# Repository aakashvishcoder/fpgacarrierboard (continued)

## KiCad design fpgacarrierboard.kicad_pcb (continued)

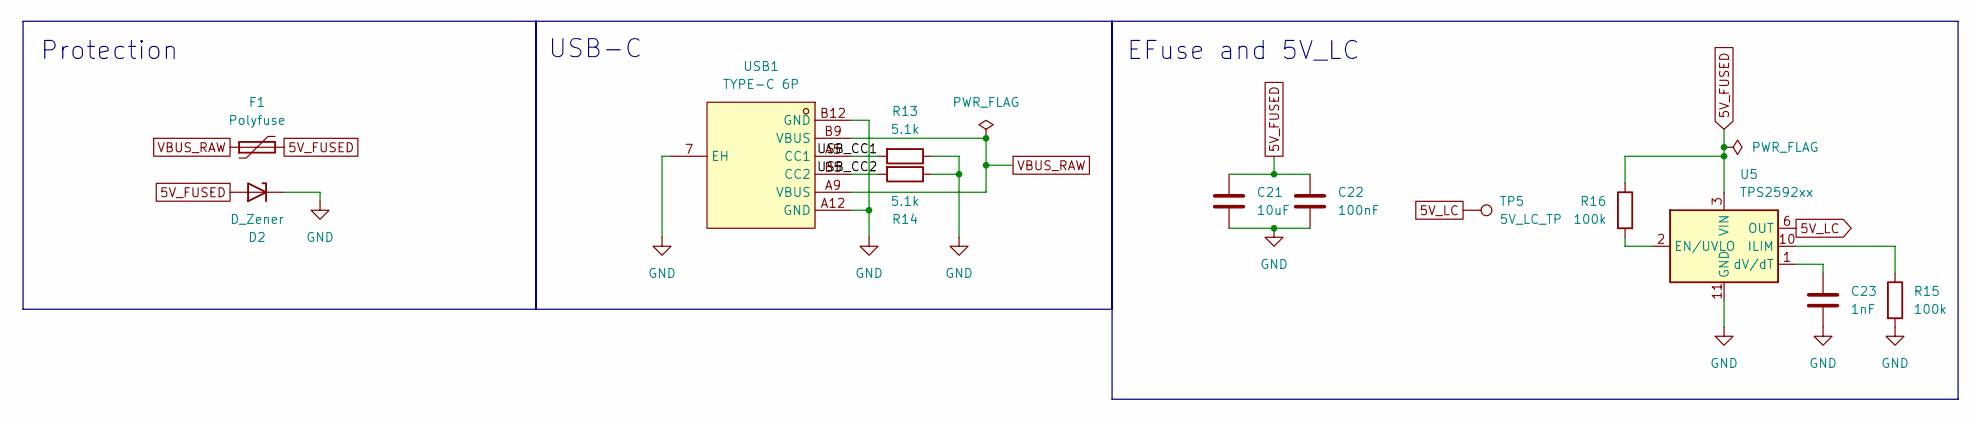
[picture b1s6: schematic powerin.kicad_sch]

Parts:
C21: 10uF; CP_Radial_D5.0mm_P2.00mm; LCSC Part C47344176
C22: 100nF; C_Disc_D3.0mm_W2.0mm_P2.50mm; LCSC Part C5632430
C23: 1nF; C_Disc_D3.0mm_W2.0mm_P2.50mm; LCSC Part C1624895
D2: D_Zener; D_DO-41_SOD81_P10.16mm_Horizontal
F1: Polyfuse; FUSE-TH_L9.5-W3.5-P5.08-D0.8-S1.2
R13, R14: 5.1k; R_Axial_DIN0207_L6.3mm_D2.5mm_P10.16mm_Horizontal
R15, R16: 100k; R_Axial_DIN0207_L6.3mm_D2.5mm_P10.16mm_Horizontal
TP5: 5V_LC_TP; TestPoint_THTPad_D1.5mm_Drill0.7mm
U5: TPS2592xx; VSON-10-1EP_3x3mm_P0.5mm_EP1.65x2.4mm; LCSC Part C527680
USB1: TYPE-C 6P; TYPE-C-SMD_TYPE-C-6P_1; MPN TYPE-C 6P; LCSC Part C456012

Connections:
5V_FUSED: C21.1, C22.1, D2.2 (A), F1.2, R16.1, U5.3 (VIN), U5.4 (VIN), U5.5 (VIN)
5V_LC: TP5.1 (1_1), U5.6 (OUT), U5.7 (OUT), U5.8 (OUT); also elsewhere on the board
/PowerIn/USB_CC1: R13.2, USB1.A5 (CC1)
/PowerIn/USB_CC2: R14.2, USB1.B5 (CC2)
GND: C21.2, C22.2, C23.2, D2.1 (K), R13.1, R14.1, R15.2, U5.11 (GND), USB1.7 (EH), USB1.A12 (GND), USB1.B12 (GND); also elsewhere on the board
unnamed: R16.2, U5.2 (EN/UVLO)
unnamed: R15.1, U5.10 (ILIM)
unnamed: C23.1, U5.1 (dV/dT)
VBUS_RAW: F1.1, USB1.A9 (VBUS), USB1.B9 (VBUS)

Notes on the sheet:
USB-C
Protection
EFuse and 5V_LC

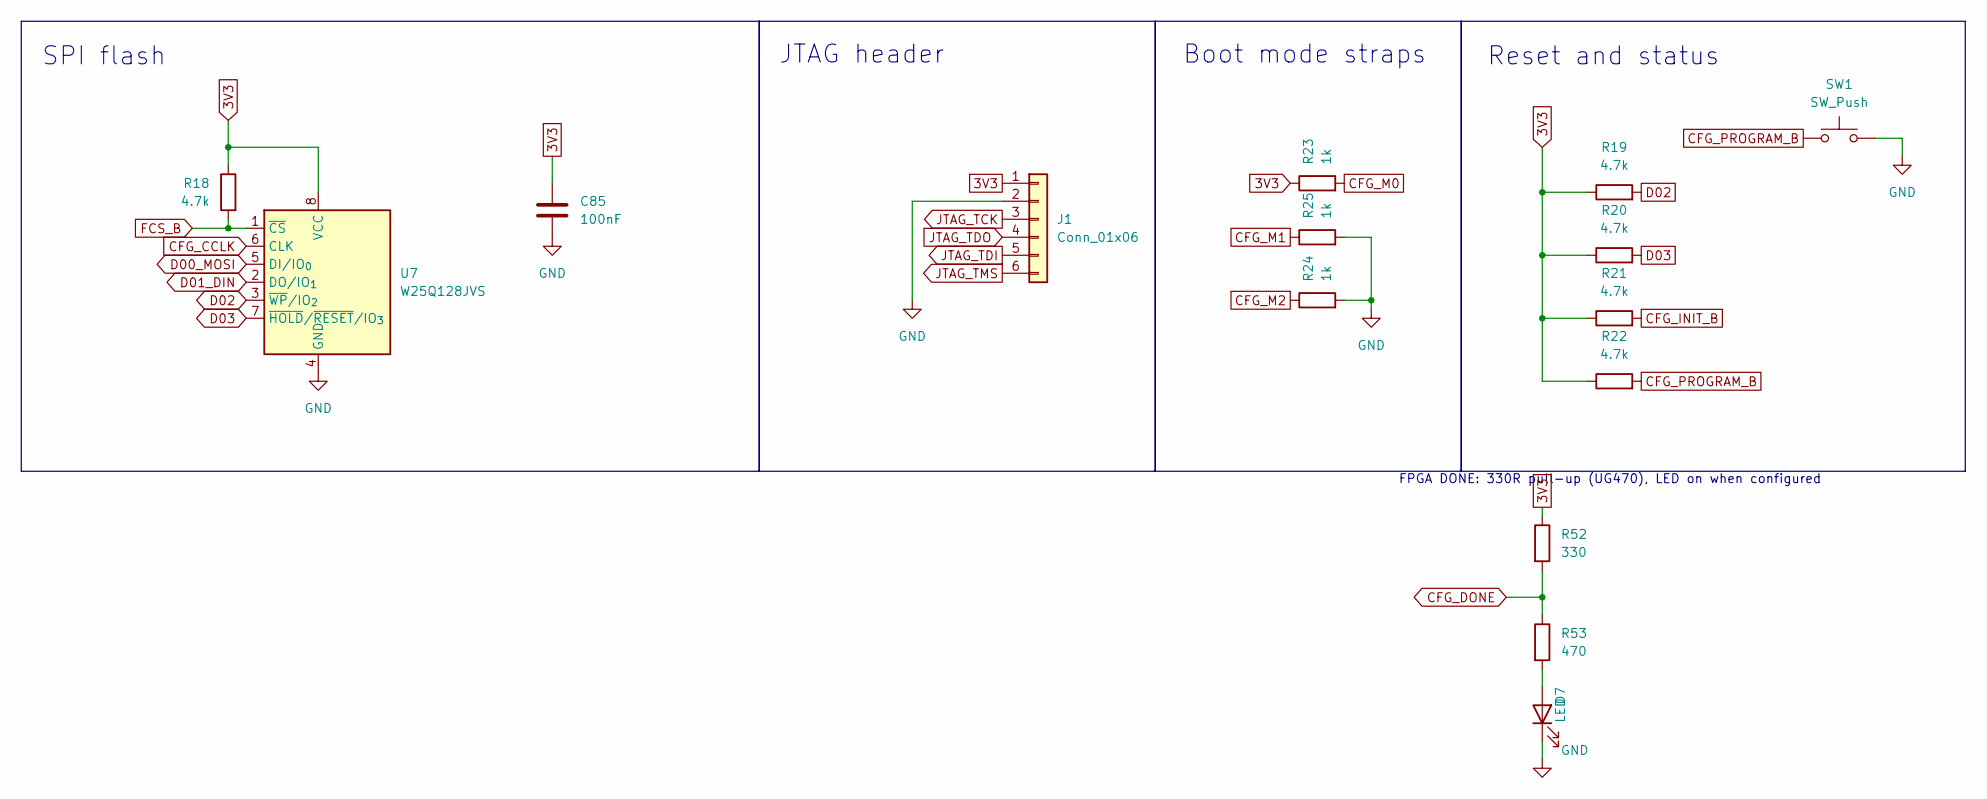
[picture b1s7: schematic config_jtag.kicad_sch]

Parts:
C85: 100nF; C_Disc_D3.0mm_W2.0mm_P2.50mm; LCSC Part C5632430
D7: LED; LED_D3.0mm
J1: Conn_01x06; PinHeader_1x06_P2.54mm_Vertical
R18, R19, R20, R21, R22: 4.7k; R_Axial_DIN0207_L6.3mm_D2.5mm_P10.16mm_Horizontal
R23, R24, R25: 1k; R_Axial_DIN0207_L6.3mm_D2.5mm_P10.16mm_Horizontal
R52: 330; R_Axial_DIN0207_L6.3mm_D2.5mm_P10.16mm_Horizontal
R53: 470; R_Axial_DIN0207_L6.3mm_D2.5mm_P10.16mm_Horizontal
SW1: SW_Push; SW_SPST_TL3342
U7: W25Q128JVS; SOIC-8_5.3x5.3mm_P1.27mm; LCSC Part C97521

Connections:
3V3: C85.1, J1.1, R18.1, R19.1, R20.1, R21.1, R22.1, R23.1, R52.1, U7.8 (VCC); also elsewhere on the board
CFG_CCLK: U7.6 (CLK); also elsewhere on the board
CFG_DONE: R52.2, R53.1; also elsewhere on the board
CFG_INIT_B: R21.2; also elsewhere on the board
CFG_M0: R23.2; also elsewhere on the board
CFG_M1: R25.1; also elsewhere on the board
CFG_M2: R24.1; also elsewhere on the board
CFG_PROGRAM_B: R22.2, SW1.1; also elsewhere on the board
D00_MOSI: U7.5 (DI/IO_{0}); also elsewhere on the board
D01_DIN: U7.2 (DO/IO_{1}); also elsewhere on the board
D02: R19.2, U7.3 (~WP/IO_{2}); also elsewhere on the board
D03: R20.2, U7.7 (~HOLD/~RESET/IO_{3}); also elsewhere on the board
FCS_B: R18.2, U7.1 (~CS); also elsewhere on the board
GND: C85.2, D7.1 (K), J1.2, R24.2, R25.2, SW1.2, U7.4 (GND); also elsewhere on the board
JTAG_TCK: J1.3; also elsewhere on the board
JTAG_TDI: J1.5; also elsewhere on the board
JTAG_TDO: J1.4; also elsewhere on the board
JTAG_TMS: J1.6; also elsewhere on the board
unnamed: D7.2 (A), R53.2

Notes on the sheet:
Reset and status
SPI flash
JTAG header
Boot mode straps
FPGA DONE: 330R pull-up (UG470), LED on when configured

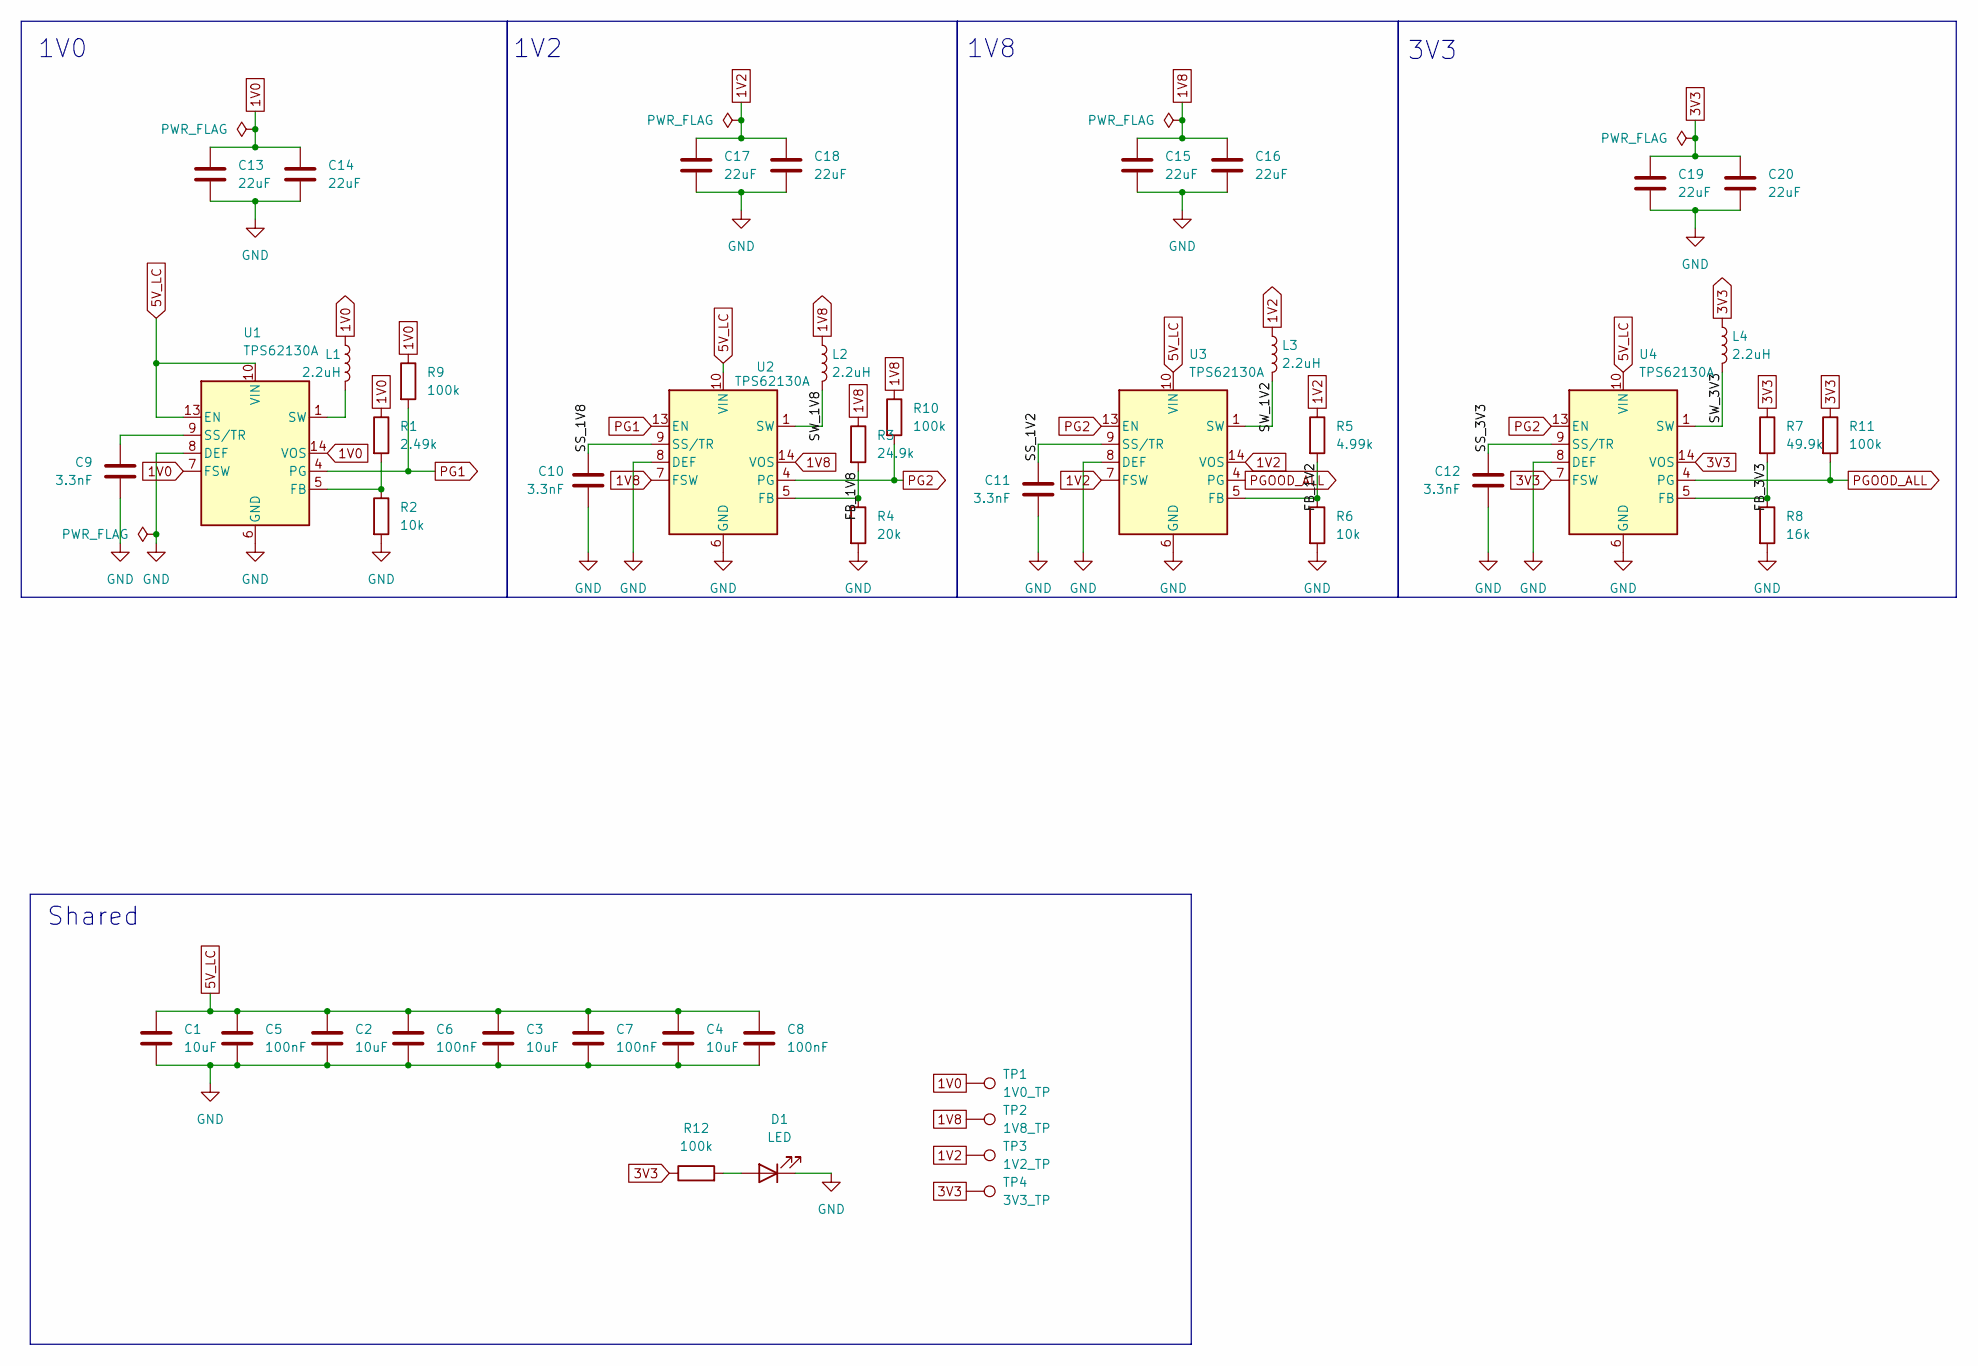
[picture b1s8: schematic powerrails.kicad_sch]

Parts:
C1, C2, C3, C4: 10uF; CP_Radial_D5.0mm_P2.00mm; LCSC Part C47344176
C5, C6, C7, C8: 100nF; C_Disc_D3.0mm_W2.0mm_P2.50mm; LCSC Part C5632430
C9, C10, C11, C12: 3.3nF; C_Disc_D3.0mm_W2.0mm_P2.50mm; LCSC Part C511575
C13, C14, C15, C16, C17, C18, C19, C20: 22uF; CP_Radial_D6.3mm_P2.50mm; LCSC Part C2835673
D1: LED; LED_D3.0mm
L1, L2, L3, L4: 2.2uH; IND-SMD_L4.5-W4.1_SRP4020TA; LCSC Part C719179
R1: 2.49k; R_Axial_DIN0207_L6.3mm_D2.5mm_P10.16mm_Horizontal
R2, R6: 10k; R_Axial_DIN0207_L6.3mm_D2.5mm_P10.16mm_Horizontal
R3: 24.9k; R_Axial_DIN0207_L6.3mm_D2.5mm_P10.16mm_Horizontal
R4: 20k; R_Axial_DIN0207_L6.3mm_D2.5mm_P10.16mm_Horizontal
R5: 4.99k; R_Axial_DIN0207_L6.3mm_D2.5mm_P10.16mm_Horizontal
R7: 49.9k; R_Axial_DIN0207_L6.3mm_D2.5mm_P10.16mm_Horizontal
R8: 16k; R_Axial_DIN0207_L6.3mm_D2.5mm_P10.16mm_Horizontal
R9, R10, R11, R12: 100k; R_Axial_DIN0207_L6.3mm_D2.5mm_P10.16mm_Horizontal
TP1: 1V0_TP; TestPoint_THTPad_D1.5mm_Drill0.7mm
TP2: 1V8_TP; TestPoint_THTPad_D1.5mm_Drill0.7mm
TP3: 1V2_TP; TestPoint_THTPad_D1.5mm_Drill0.7mm
TP4: 3V3_TP; TestPoint_THTPad_D1.5mm_Drill0.7mm
U1, U2, U3, U4: TPS62130A; VQFN-16-1EP_3x3mm_P0.5mm_EP1.68x1.68mm; LCSC Part C337502

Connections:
1V0: C13.1, C14.1, L1.1, R1.1, R9.1, TP1.1 (1_1), U1.7 (FSW), U1.14 (VOS); also elsewhere on the board
1V2: C17.1, C18.1, L3.1, R5.1, TP3.1 (1_1), U3.7 (FSW), U3.14 (VOS); also elsewhere on the board
1V8: C15.1, C16.1, L2.1, R3.1, R10.1, TP2.1 (1_1), U2.7 (FSW), U2.14 (VOS); also elsewhere on the board
3V3: C19.1, C20.1, L4.1, R7.1, R11.1, R12.1, TP4.1 (1_1), U4.7 (FSW), U4.14 (VOS); also elsewhere on the board
5V_LC: C1.1, C2.1, C3.1, C4.1, C5.1, C6.1, C7.1, C8.1, U1.10 (VIN), U1.11 (VIN), U1.12 (VIN), U1.13 (EN), U2.10 (VIN), U2.11 (VIN), U2.12 (VIN), U3.10 (VIN), U3.11 (VIN), U3.12 (VIN), U4.10 (VIN), U4.11 (VIN), U4.12 (VIN); also elsewhere on the board
/Power_Rails/FB_1V2: R5.2, R6.1, U3.5 (FB)
/Power_Rails/FB_1V8: R3.2, R4.1, U2.5 (FB)
/Power_Rails/FB_3V3: R7.2, R8.1, U4.5 (FB)
/Power_Rails/SS_1V2: C11.1, U3.9 (SS/TR)
/Power_Rails/SS_1V8: C10.1, U2.9 (SS/TR)
/Power_Rails/SS_3V3: C12.1, U4.9 (SS/TR)
/Power_Rails/SW_1V2: L3.2, U3.1 (SW), U3.2 (SW), U3.3 (SW)
/Power_Rails/SW_1V8: L2.2, U2.1 (SW), U2.2 (SW), U2.3 (SW)
/Power_Rails/SW_3V3: L4.2, U4.1 (SW), U4.2 (SW), U4.3 (SW)
GND: C1.2, C2.2, C3.2, C4.2, C5.2, C6.2, C7.2, C8.2, C9.2, C10.2, C11.2, C12.2, C13.2, C14.2, C15.2, C16.2, C17.2, C18.2, C19.2, C20.2, D1.1 (K), R2.2, R4.2, R6.2, R8.2, U1.6 (GND), U1.8 (DEF), U1.15 (GND), U1.16 (GND), U1.17 (GND), U2.6 (GND), U2.8 (DEF), U2.15 (GND), U2.16 (GND), U2.17 (GND), U3.6 (GND), U3.8 (DEF), U3.15 (GND), U3.16 (GND), U3.17 (GND), U4.6 (GND), U4.8 (DEF), U4.15 (GND), U4.16 (GND), U4.17 (GND); also elsewhere on the board
unnamed: D1.2 (A), R12.2
unnamed: L1.2, U1.1 (SW), U1.2 (SW), U1.3 (SW)
unnamed: R1.2, R2.1, U1.5 (FB)
unnamed: C9.1, U1.9 (SS/TR)
PG1: R9.2, U1.4 (PG), U2.13 (EN)
PG2: R10.2, U2.4 (PG), U3.13 (EN), U4.13 (EN)
PGOOD_ALL: R11.2, U3.4 (PG), U4.4 (PG)

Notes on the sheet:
1V8
3V3
1V0
1V2
Shared

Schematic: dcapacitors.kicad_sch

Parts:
C24: 100uF; C_1210_3225Metric; LCSC Part C49066
C25, C26, C27, C28, C29: 47uF; C_1210_3225Metric; LCSC Part C2932477
C30, C31, C32, C33, C34, C35, C36, C37, C38, C39, C40, C41, C42, C43, C44, C45, C46: 4.7uF; C_0805_2012Metric; LCSC Part C98195
C47, C48, C49, C50, C51, C52, C53, C54, C55, C56, C57, C58, C59, C60, C61, C62, C63, C64, C65, C66, C67, C68, C69, C70, C71, C72, C73, C74, C75, C76, C77, C78: 0.47uF; C_0603_1608Metric; LCSC Part C1623

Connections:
1V0: C24.1, C25.1, C30.1, C31.1, C47.1, C48.1, C49.1; also elsewhere on the board
1V8: C26.1, C32.1, C33.1, C50.1, C51.1, C52.1, C53.1, C54.1; also elsewhere on the board
3V3: C27.1, C28.1, C29.1, C34.1, C35.1, C36.1, C37.1, C38.1, C39.1, C40.1, C41.1, C42.1, C43.1, C44.1, C45.1, C46.1, C55.1, C56.1, C57.1, C58.1, C59.1, C60.1, C61.1, C62.1, C63.1, C64.1, C65.1, C66.1, C67.1, C68.1, C69.1, C70.1, C71.1, C72.1, C73.1, C74.1, C75.1, C76.1, C77.1, C78.1; also elsewhere on the board
GND: C24.2, C25.2, C26.2, C27.2, C28.2, C29.2, C30.2, C31.2, C32.2, C33.2, C34.2, C35.2, C36.2, C37.2, C38.2, C39.2, C40.2, C41.2, C42.2, C43.2, C44.2, C45.2, C46.2, C47.2, C48.2, C49.2, C50.2, C51.2, C52.2, C53.2, C54.2, C55.2, C56.2, C57.2, C58.2, C59.2, C60.2, C61.2, C62.2, C63.2, C64.2, C65.2, C66.2, C67.2, C68.2, C69.2, C70.2, C71.2, C72.2, C73.2, C74.2, C75.2, C76.2, C77.2, C78.2; also elsewhere on the board

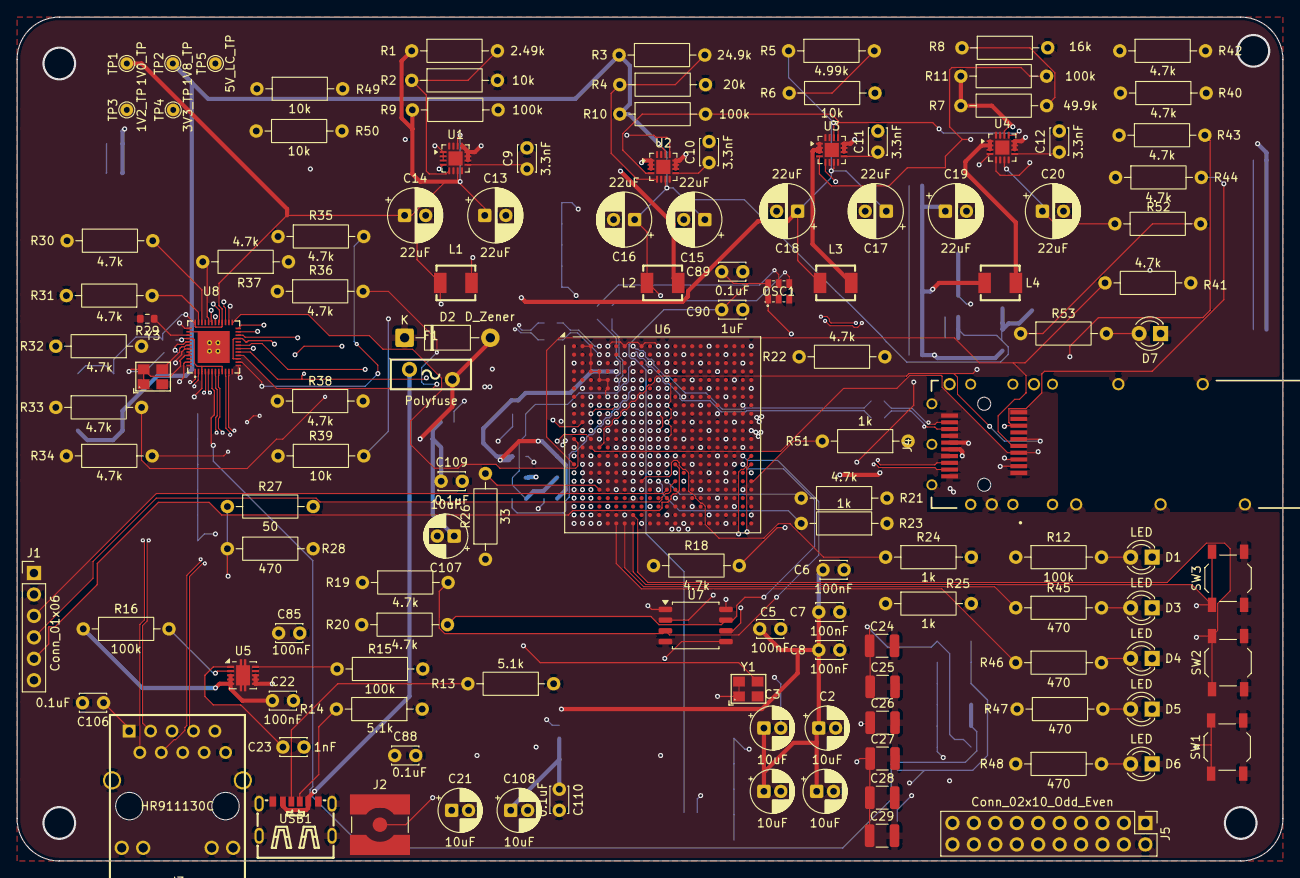
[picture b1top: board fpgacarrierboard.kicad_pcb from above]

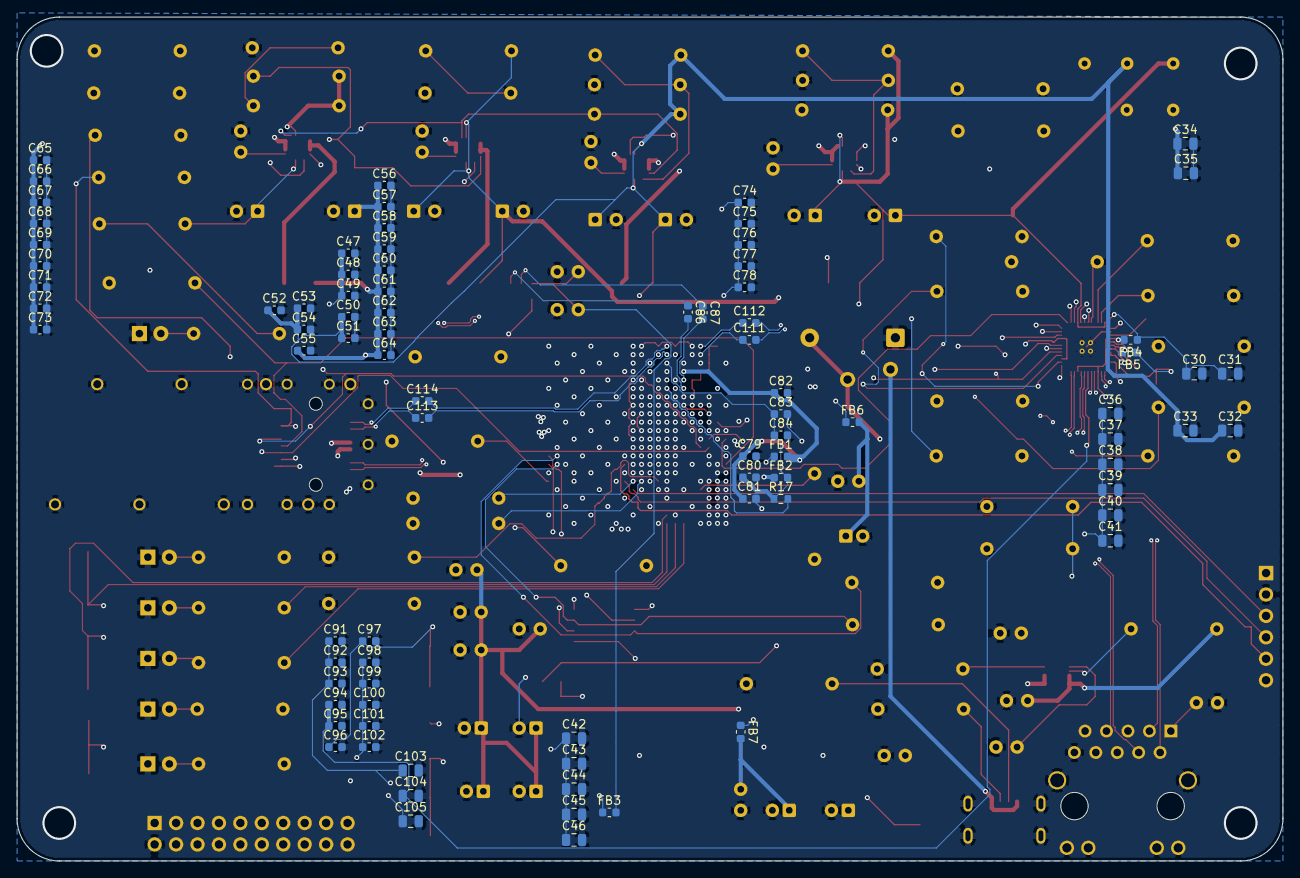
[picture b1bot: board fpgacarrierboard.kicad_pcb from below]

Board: 6 copper layers, 150.0 x 100.0 mm, 211 parts (84 on the bottom side), 134 nets.

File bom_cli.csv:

"Reference","Value","Footprint","Qty","LCSC"
"C1-C4,C21,C107,C108","10uF","Capacitor_THT:CP_Radial_D5.0mm_P2.00mm","7","C47344176"
"C5-C8,C22,C85","100nF","Capacitor_THT:C_Disc_D3.0mm_W2.0mm_P2.50mm","6","C5632430"
"C9-C12","3.3nF","Capacitor_THT:C_Disc_D3.0mm_W2.0mm_P2.50mm","4","C511575"
"C13-C20","22uF","Capacitor_THT:CP_Radial_D6.3mm_P2.50mm","8","C2835673"
"C23","1nF","Capacitor_THT:C_Disc_D3.0mm_W2.0mm_P2.50mm","1","C1624895"
"C24","100uF","Capacitor_SMD:C_1210_3225Metric","1","C49066"
"C25-C29","47uF","Capacitor_SMD:C_1210_3225Metric","5","C2932477"
"C30-C46,C103-C105","4.7uF","Capacitor_SMD:C_0805_2012Metric","20","C98195"
"C47-C78","0.47uF","Capacitor_SMD:C_0603_1608Metric","32","C1623"
"C79,C80","4.7uF","Capacitor_SMD:C_0603_1608Metric","2","C107368"
"C81-C84,C86,C87,C91-C102,C111-C114","0.1uF","Capacitor_SMD:C_0603_1608Metric","22","C14663"
"C88,C89,C106,C109,C110","0.1uF","Capacitor_THT:C_Disc_D3.0mm_W2.0mm_P2.50mm","5","C5632430"
"C90","1uF","Capacitor_THT:C_Disc_D3.0mm_W2.0mm_P2.50mm","1","C1646109"
"D1,D3-D6","LED","LED_THT:LED_D3.0mm","5",""
"D2","D_Zener","Diode_THT:D_DO-41_SOD81_P10.16mm_Horizontal","1",""
"F1","Polyfuse","easyeda:FUSE-TH_L9.5-W3.5-P5.08-D0.8-S1.2","1",""
"FB1-FB7","FerriteBead","Inductor_SMD:L_0603_1608Metric","7","C19330"
"J1","Conn_01x06","Connector_PinHeader_2.54mm:PinHeader_1x06_P2.54mm_Vertical","1",""
"J2","Conn_Coaxial","Connector_Coaxial:SMA_Amphenol_132134-10_Vertical","1","C2693814"
"J3","HR911130C","easyeda:RJ45-TH_HR911130C","1","C50933"
"J4","SFPK-SL","samtec:SAMTEC_SFPK-SL","1","C20691304"
"J5","Conn_02x10_Odd_Even","Connector_PinHeader_2.54mm:PinHeader_2x10_P2.54mm_Vertical","1",""
"L1-L4","2.2uH","easyeda:IND-SMD_L4.5-W4.1_SRP4020TA","4","C719179"
"OSC1","OB2EL89CLIB112YLC-125M","easyeda:OSC-SMD_6P-L3.2-W2.5-BL-1","1","C7425465"
"R1","2.49k","Resistor_THT:R_Axial_DIN0207_L6.3mm_D2.5mm_P10.16mm_Horizontal","1",""
"R2,R6,R39,R49,R50","10k","Resistor_THT:R_Axial_DIN0207_L6.3mm_D2.5mm_P10.16mm_Horizontal","5",""
"R3","24.9k","Resistor_THT:R_Axial_DIN0207_L6.3mm_D2.5mm_P10.16mm_Horizontal","1",""
"R4","20k","Resistor_THT:R_Axial_DIN0207_L6.3mm_D2.5mm_P10.16mm_Horizontal","1",""
"R5","4.99k","Resistor_THT:R_Axial_DIN0207_L6.3mm_D2.5mm_P10.16mm_Horizontal","1",""
"R7","49.9k","Resistor_THT:R_Axial_DIN0207_L6.3mm_D2.5mm_P10.16mm_Horizontal","1",""
"R8","16k","Resistor_THT:R_Axial_DIN0207_L6.3mm_D2.5mm_P10.16mm_Horizontal","1",""
"R9-R12,R15,R16","100k","Resistor_THT:R_Axial_DIN0207_L6.3mm_D2.5mm_P10.16mm_Horizontal","6",""
"R13,R14","5.1k","Resistor_THT:R_Axial_DIN0207_L6.3mm_D2.5mm_P10.16mm_Horizontal","2",""
"R17","100","Resistor_SMD:R_0603_1608Metric","1","C2906981"
"R18-R22,R30-R38,R40-R44,R51","4.7k","Resistor_THT:R_Axial_DIN0207_L6.3mm_D2.5mm_P10.16mm_Horizontal","20",""
"R23-R25","1k","Resistor_THT:R_Axial_DIN0207_L6.3mm_D2.5mm_P10.16mm_Horizontal","3",""
"R26","33","Resistor_THT:R_Axial_DIN0207_L6.3mm_D2.5mm_P10.16mm_Horizontal","1",""
"R27","50","Resistor_THT:R_Axial_DIN0207_L6.3mm_D2.5mm_P10.16mm_Horizontal","1",""
"R28,R45-R48","470","Resistor_THT:R_Axial_DIN0207_L6.3mm_D2.5mm_P10.16mm_Horizontal","5",""
"R29","2.49k","Resistor_SMD:R_0603_1608Metric","1","C2930072"
"SW1-SW3","SW_Push","Button_Switch_SMD:SW_SPST_TL3342","3",""
"TP1","1V0_TP","TestPoint:TestPoint_THTPad_D1.5mm_Drill0.7mm","1",""
"TP2","1V8_TP","TestPoint:TestPoint_THTPad_D1.5mm_Drill0.7mm","1",""
"TP3","1V2_TP","TestPoint:TestPoint_THTPad_D1.5mm_Drill0.7mm","1",""
"TP4","3V3_TP","TestPoint:TestPoint_THTPad_D1.5mm_Drill0.7mm","1",""
"TP5","TestPoint","TestPoint:TestPoint_THTPad_D1.5mm_Drill0.7mm","1",""
"U1-U4","TPS62130A","Package_DFN_QFN:VQFN-16-1EP_3x3mm_P0.5mm_EP1.68x1.68mm","4","C337502"
"U5","TPS2592xx","Package_SON:VSON-10-1EP_3x3mm_P0.5mm_EP1.65x2.4mm","1","C527680"
"U6","XC7A35T-FGG484","Package_BGA:Xilinx_FGG484","1","C6934285"
"U7","W25Q128JVS","Package_SO:SOIC-8_5.3x5.3mm_P1.27mm","1","C97521"
"U8","RTL8211E-VB-CG","easyeda:QFN-48_L6.0-W6.0-P0.40-BL-EP3.8","1","C90735"
"USB1","TYPE-C 6P","easyeda:TYPE-C-SMD_TYPE-C-6P_1","1","C456012"
"Y1","OT322550MJBA4SL","easyeda:OSC-SMD_4P-L3.2-W2.5-BL","1","C717684"
"Y3","OT322525MJBA4SL","easyeda:OSC-SMD_4P-L3.2-W2.5-BL","1","C669088"
